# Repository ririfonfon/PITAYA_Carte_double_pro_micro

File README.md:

# PITAYA_Carte_double_pro_micro
 Carte double pro micro

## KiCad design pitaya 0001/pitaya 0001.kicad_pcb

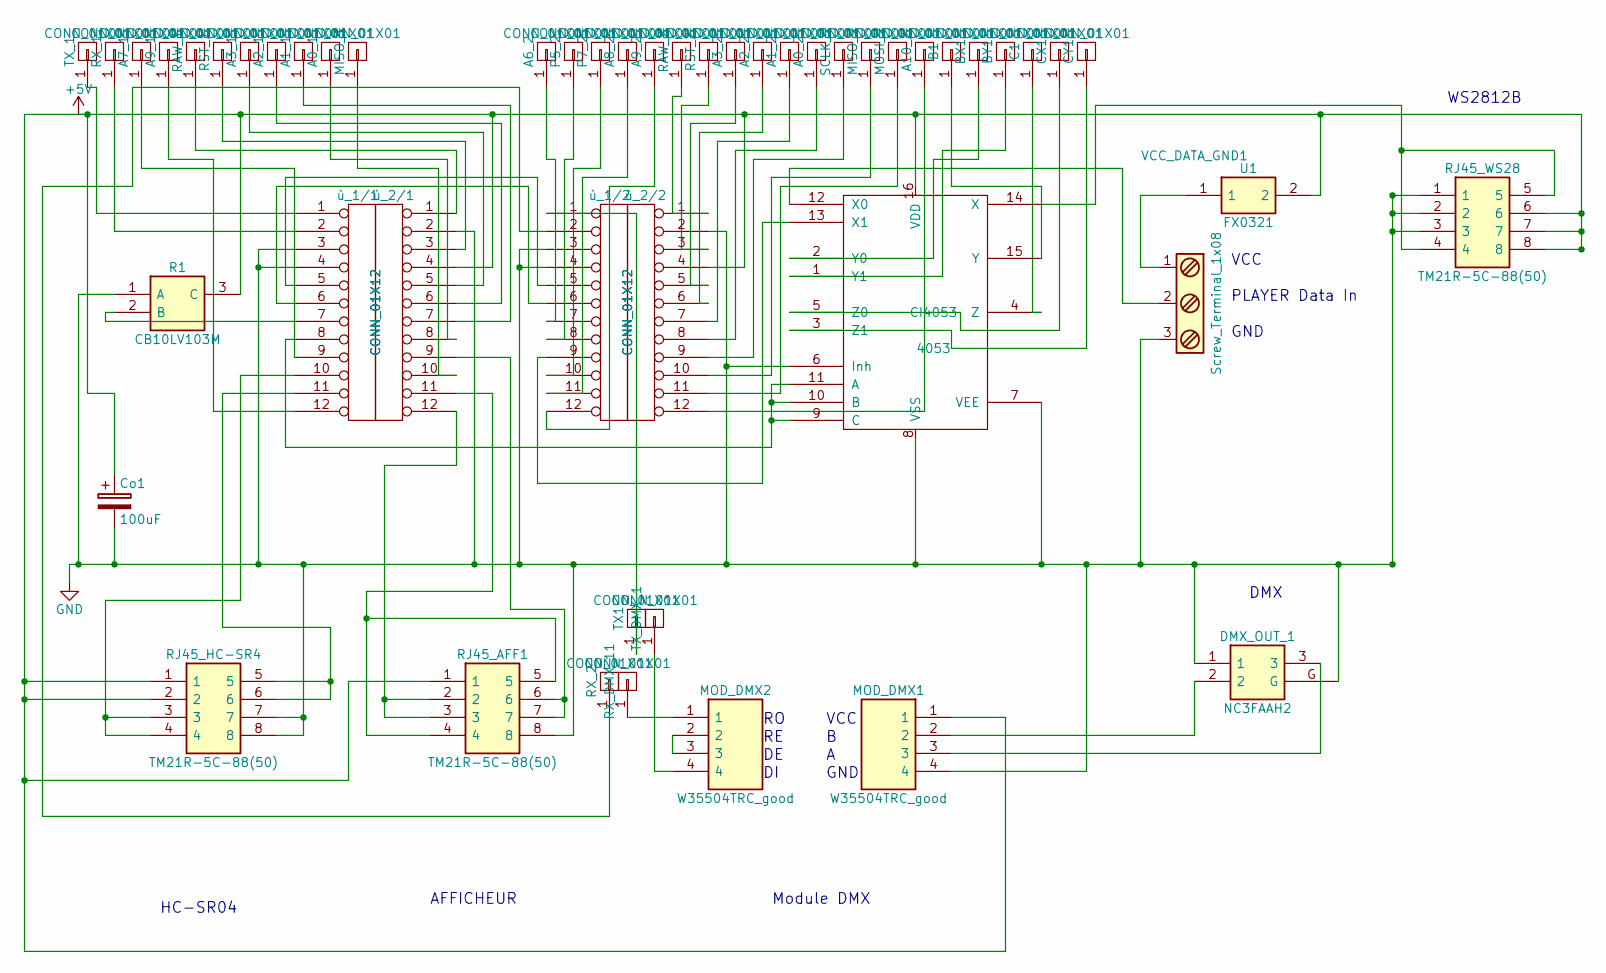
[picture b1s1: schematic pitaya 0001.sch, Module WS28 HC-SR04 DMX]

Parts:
A0_1, A0_2, A1_1, A1_2, A2_1, A2_2, A3_1, A3_2, A6_2, A7_1, A8_2, A9_1, A9_2, A10_2: CONN_01X01; j_1_pin
B1: CONN_01X01; j_1_pin
BX1: CONN_01X01; j_1_pin
BY1: CONN_01X01; j_1_pin
C1: CONN_01X01; j_1_pin
CI4053: 4053; DIP-16_W7.62mm_Socket
CX1: CONN_01X01; j_1_pin
CY1: CONN_01X01; j_1_pin
Co1: 100uF; CP_Radial_D6.3mm_P2.50mm
DMX_OUT_1: NC3FAAH2; NC3FAAH2_2; Manufacturer_Part_Number NC3FAAH2
MISO_1, MISO_2: CONN_01X01; j_1_pin
MOD_DMX1, MOD_DMX2: W35504TRC_good; SHDR04; Manufacturer_Part_Number W35520TRC
MOSI_2: CONN_01X01; j_1_pin
P5_2, P7_2: CONN_01X01; j_1_pin
R1: CB10LV103M; Manufacturer_Part_Number CB10LV103M
RAW_1, RAW_2: CONN_01X01; j_1_pin
RJ45_AFF1, RJ45_HC-SR4, RJ45_WS28: TM21R-5C-88(50); TM21R-5C-88(riri); Manufacturer_Part_Number TM21R-5C-88(50)
RST_1, RST_2: CONN_01X01; j_1_pin
RX_1, RX_2: CONN_01X01; j_1_pin
RX_DMX_11: CONN_01X01; j_1_pin
SCLK_2: CONN_01X01; j_1_pin
TX1: CONN_01X01; j_1_pin
TX_1: CONN_01X01; j_1_pin
TX_DMX_1: CONN_01X01; j_1_pin
U1: FX0321; Manufacturer_Part_Number FX0321
VCC_DATA_GND1: Screw_Terminal_1x08; TerminalBlock_4UCON_19963_03x3.5mm_Straight
ù_1/1, ù_1/2, ù_2/1, ù_2/2: CONN_01X12; Pin_Header_Straight_1x12_Pitch2.54mm

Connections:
unnamed: A0_1.1, ù_2/1.8
unnamed: A0_2.1, ù_2/2.8
unnamed: A1_1.1, ù_2/1.7
unnamed: A1_2.1, ù_2/2.7
unnamed: A2_1.1, ù_2/1.6
unnamed: A2_2.1, ù_2/2.6
unnamed: A3_1.1, ù_2/1.5
unnamed: A3_2.1, ù_2/2.5
unnamed: A6_2.1, ù_1/2.7
unnamed: A7_1.1, ù_1/1.9
unnamed: A8_2.1, ù_1/2.11
unnamed: A9_1.1, ù_1/1.12
unnamed: A9_2.1, ù_1/2.12
unnamed: A10_2.1, ù_2/2.12
unnamed: B1.1, CI4053.15 (Y)
unnamed: BX1.1, CI4053.2 (Y0)
unnamed: BY1.1, CI4053.1 (Y1)
unnamed: C1.1, CI4053.4 (Z)
unnamed: CI4053.3 (Z1), CY1.1
unnamed: CI4053.5 (Z0), CX1.1
unnamed: CI4053.6 (Inh), CI4053.7 (VEE), CI4053.8 (VSS), Co1.2, DMX_OUT_1.1, DMX_OUT_1.G, MOD_DMX1.4, R1.1 (A), RJ45_AFF1.8, RJ45_HC-SR4.7, RJ45_HC-SR4.8, RJ45_WS28.1, RJ45_WS28.2, RJ45_WS28.3, VCC_DATA_GND1.3, ù_1/1.3, ù_1/1.4, ù_1/2.3, ù_1/2.4, ù_2/1.2, ù_2/2.2
unnamed: CI4053.9 (C), CI4053.10 (B), CI4053.11 (A), ù_1/1.8
unnamed: CI4053.12 (X0), VCC_DATA_GND1.2
unnamed: CI4053.13 (X1), ù_1/2.9
unnamed: CI4053.14 (X), RJ45_WS28.4, RJ45_WS28.5
unnamed: CI4053.16 (VDD), Co1.1, MOD_DMX1.1, R1.3 (C), RJ45_AFF1.1, RJ45_HC-SR4.1, RJ45_HC-SR4.2, RJ45_WS28.6, RJ45_WS28.7, RJ45_WS28.8, U1.2, ù_2/1.4, ù_2/2.4
unnamed: DMX_OUT_1.2, MOD_DMX1.2
unnamed: DMX_OUT_1.3, MOD_DMX1.3
unnamed: MISO_1.1, ù_2/1.10
unnamed: MISO_2.1, ù_2/2.10
unnamed 30: MOD_DMX2.1, RX_DMX_11.1; also elsewhere on the board
unnamed: MOD_DMX2.2, MOD_DMX2.3
unnamed 32: MOD_DMX2.4, TX_DMX_1.1; also elsewhere on the board
unnamed: MOSI_2.1, ù_2/2.11
unnamed: P5_2.1, ù_1/2.8
unnamed: P7_2.1, ù_1/2.10
unnamed: R1.2 (B), ù_1/1.7
unnamed: RAW_1.1, ù_2/1.1
unnamed: RAW_2.1, ù_2/2.1
unnamed: RJ45_AFF1.2, RJ45_AFF1.3, ù_2/1.12
unnamed: RJ45_AFF1.4, RJ45_AFF1.5, ù_2/1.11
unnamed: RJ45_AFF1.6, RJ45_AFF1.7, ù_2/1.9
unnamed: RJ45_HC-SR4.3, RJ45_HC-SR4.4, ù_1/1.10
unnamed: RJ45_HC-SR4.5, RJ45_HC-SR4.6, ù_1/1.11
unnamed: RST_1.1, ù_2/1.3
unnamed: RST_2.1, ù_2/2.3
unnamed: RX_1.1, ù_1/1.2
unnamed 47: RX_2.1, ù_1/2.2; also elsewhere on the board
unnamed: SCLK_2.1, ù_2/2.9
unnamed 49: TX1.1, ù_1/2.1; also elsewhere on the board
unnamed: TX_1.1, ù_1/1.1
unnamed: U1.1, VCC_DATA_GND1.1
unnamed: ù_1/1.5, ù_1/2.5
unnamed: ù_1/1.6, ù_1/2.6

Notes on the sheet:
WS2812B
DMX
HC-SR04
AFFICHEUR
VCC
GND
Module DMX
PLAYER Data In

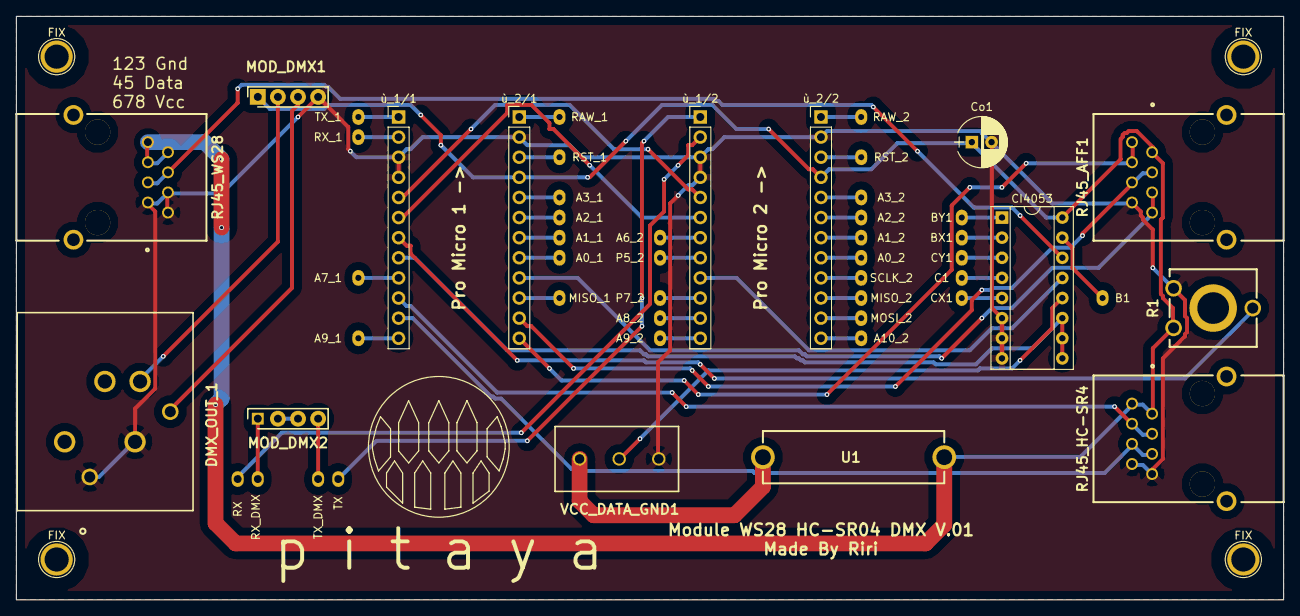
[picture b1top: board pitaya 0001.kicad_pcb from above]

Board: 2 copper layers, 160.0 x 73.7 mm, 55 parts (0 on the bottom side), 54 nets.

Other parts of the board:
FIX: 1pin
FIX#2, FIX#3, FIX#4: 1pin
RX: CONN_01X01; j_1_pin
RX_DMX: CONN_01X01; j_1_pin
TX: CONN_01X01; j_1_pin
TX_DMX: CONN_01X01; j_1_pin

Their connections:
unnamed 30: RX_DMX.1; also elsewhere on the board
unnamed 32: TX_DMX.1; also elsewhere on the board
unnamed 47: RX.1; also elsewhere on the board
unnamed 49: TX.1; also elsewhere on the board

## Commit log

2021-07-04 pitaya_hr_001 in vscode platformio
2021-07-04 pitaya_ws2812_002_150led on vscode platformio
